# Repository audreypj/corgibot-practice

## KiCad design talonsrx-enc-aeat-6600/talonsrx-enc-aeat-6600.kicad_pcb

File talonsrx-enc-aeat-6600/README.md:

talonsrx-enc-aeat-6600
======================

A TalonSRX-compatible magnetic encoder with quadrature/incremental (A/B/I) and analog/absolute (PWM + cap) position output. This design implements the [AEAT-6600 sensor](https://github.com/ihartwig/frc-on-ftc-hw/blob/main/datasheets/AV02-2792EN-Data-Sheet-AEAT-6600-T16-2022-02-23.pdf) to use these outputs while also making the SSI/OTP pins available on a removable 6-pin programming header.

Accessing desired modes may (TBD?) [require OTP programming](https://github.com/ihartwig/frc-on-ftc-hw/blob/main/datasheets/av02-2791en_an_5501_aeat-6600_2014-04-21.pdf). It looks like the defaults are 8 CPR ABI incremental and no PWM absolute output.

The PCB is designed with 2 use cases in mind, though others may be possible
* (default) 3.3V operation from the [Data Port](https://store.ctr-electronics.com/content/user-manual/Talon%20SRX%20User's%20Guide.pdf) 0.05" pin header for incremental seeded by absolute position - HW default
    * Note that the Analog Input and Quadrature Index pins (3 & 9) differ between the TalonSRX and [Mag Encoder docs](https://store.ctr-electronics.com/content/user-manual/Magnetic%20Encoder%20User%27s%20Guide.pdf), so this design implements the pins described in the Mag Encoder docs to attempt compatibility.
* 5V operation from the 0.1" pin header for absolute position only - modify solder jumpers for 5V usage

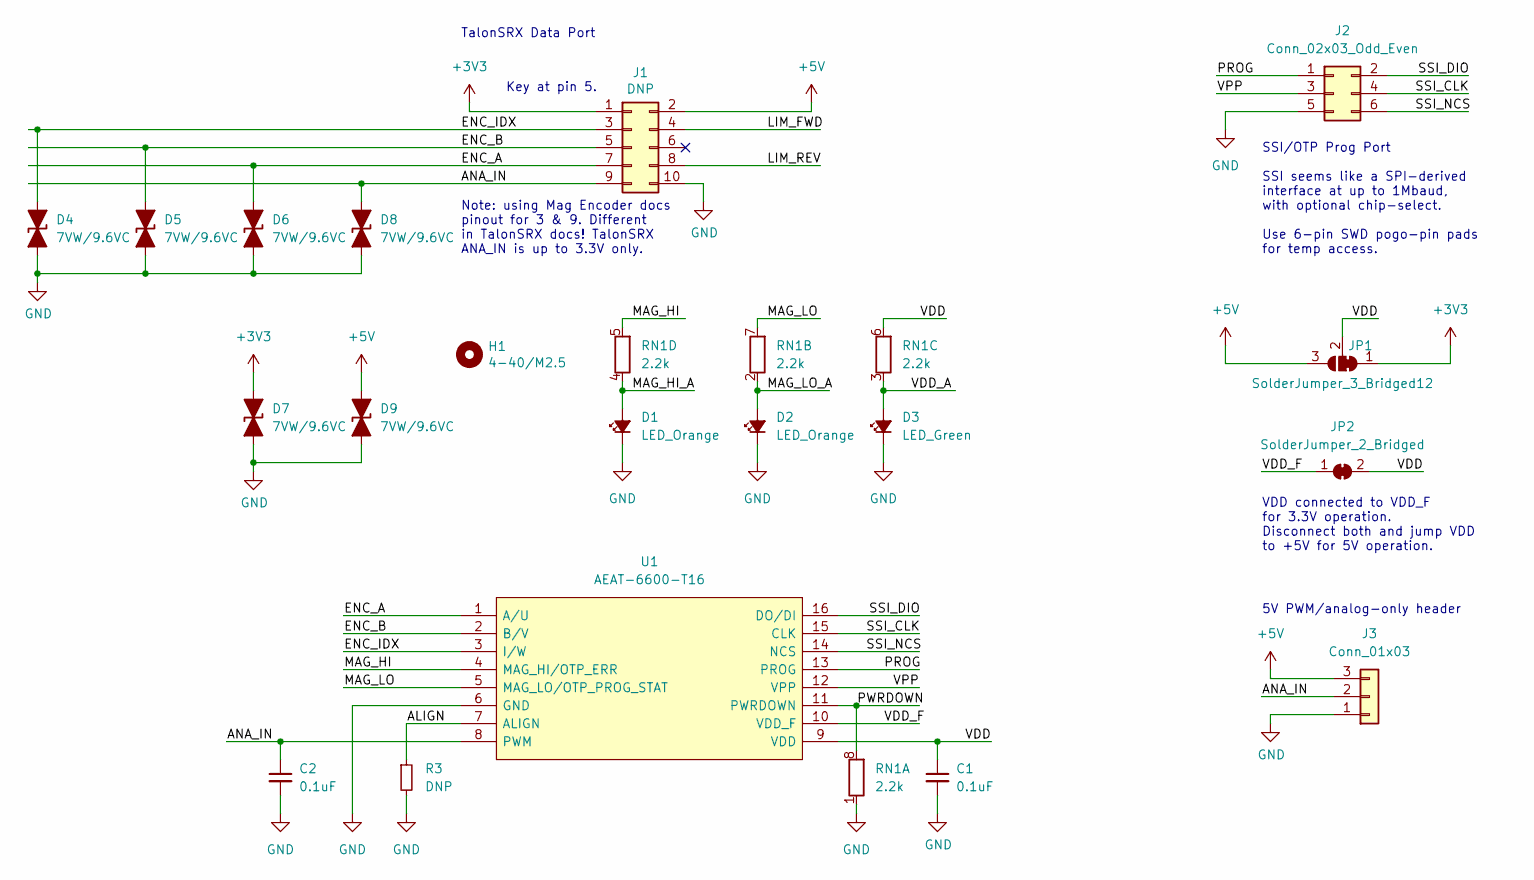
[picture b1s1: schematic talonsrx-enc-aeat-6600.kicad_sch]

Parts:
C1, C2: 0.1uF; C_0805_2012Metric
D1, D2: LED_Orange; LED_0603_1608Metric_FromBehind
D3: LED_Green; LED_0603_1608Metric_FromBehind
D4, D5, D6, D7, D8, D9: 7VW/9.6VC; D_0402_1005Metric_Pad0.77x0.64mm_HandSolder; Mfg PN PESD7V0L1BSLAZ
H1: 4-40/M2.5; MountingHole_2.7mm_M2.5
J1: DNP; PinHeader_2x05_P1.27mm_Vertical; Mfg PN 3221-10-0100-00
J2: Conn_02x03_Odd_Even; TC2030-NL_SMALL
J3: Conn_01x03; PinHeader_1x03_P2.54mm_Vertical
JP1: SolderJumper_3_Bridged12; SolderJumper-3_P1.3mm_Bridged12_RoundedPad1.0x1.5mm
JP2: SolderJumper_2_Bridged; SolderJumper-2_P1.3mm_Bridged_RoundedPad1.0x1.5mm
R3: DNP; R_0805_2012Metric
RN1: 2.2k; R_Array_Convex_4x0603; Mfg PN YC164-JR-072K2L
U1: AEAT-6600-T16; AEAT-6600-T16-SOP65P640X120-16N; Mfg PN AEAT-6600-T16; Mouser Part Number 630-AEAT-6600-T16

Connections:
+3V3: D7.1 (A1), J1.1, JP1.1 (A)
+5V: D9.1 (A1), J1.2, J3.3, JP1.3 (B)
/ALIGN: R3.1, U1.7 (ALIGN)
/ANA_IN: C2.1, D8.1 (A1), J1.9, J3.2, U1.8 (PWM)
/ENC_A: D6.1 (A1), J1.7, U1.1 (A/U)
/ENC_B: D5.1 (A1), J1.5, U1.2 (B/V)
/ENC_IDX: D4.1 (A1), J1.3, U1.3 (I/W)
/LIM_FWD: J1.4
/LIM_REV: J1.8
/MAG_HI: RN1.5 (R1.2), U1.4 (MAG_HI/OTP_ERR)
/MAG_HI_A: D1.2 (A), RN1.4 (R1.1)
/MAG_LO: RN1.7 (R1.2), U1.5 (MAG_LO/OTP_PROG_STAT)
/MAG_LO_A: D2.2 (A), RN1.2 (R1.1)
/PROG: J2.1, U1.13 (PROG)
/PWRDOWN: RN1.8 (R1.2), U1.11 (PWRDOWN)
/SSI_CLK: J2.4, U1.15 (CLK)
/SSI_DIO: J2.2, U1.16 (DO/DI)
/SSI_NCS: J2.6, U1.14 (NCS)
/VDD: C1.1, JP1.2 (C), JP2.2 (B), RN1.6 (R1.2), U1.9 (VDD)
/VDD_A: D3.2 (A), RN1.3 (R1.1)
/VDD_F: JP2.1 (A), U1.10 (VDD_F)
/VPP: J2.3, U1.12 (VPP)
GND: C1.2, C2.2, D1.1 (K), D2.1 (K), D3.1 (K), D4.2 (A2), D5.2 (A2), D6.2 (A2), D7.2 (A2), D8.2 (A2), D9.2 (A2), J1.10, J2.5, J3.1, R3.2, RN1.1 (R1.1), U1.6 (GND)

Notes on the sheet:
5V PWM/analog-only header
SSI/OTP Prog Port SSI seems like a SPI-derived interface at up to 1Mbaud, with optional chip-select. Use 6-pin SWD pogo-pin pads for temp access.
Key at pin 5.
TalonSRX Data Port
VDD connected to VDD_F for 3.3V operation. Disconnect both and jump VDD to +5V for 5V operation.
Note: using Mag Encoder docs pinout for 3 & 9. Different in TalonSRX docs! TalonSRX ANA_IN is up to 3.3V only.

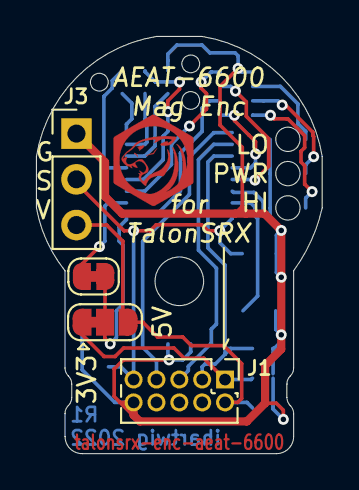
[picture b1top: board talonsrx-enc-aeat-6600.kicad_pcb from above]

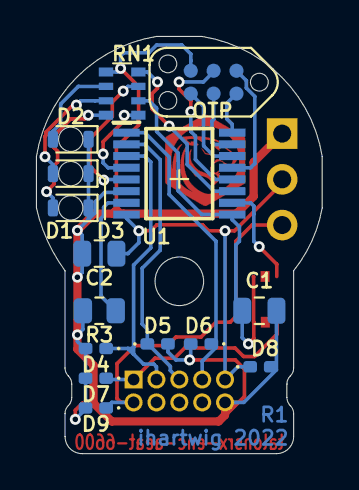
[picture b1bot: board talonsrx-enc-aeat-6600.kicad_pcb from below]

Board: 2 copper layers, 15.9 x 23.2 mm, 20 parts (15 on the bottom side), 21 nets.

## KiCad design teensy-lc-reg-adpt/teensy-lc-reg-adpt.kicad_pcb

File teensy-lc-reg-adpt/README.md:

teensy-lc-reg-adpt
==================

A backpack pcb for the [TeensyLC board](https://www.pjrc.com/teensy/teensyLC.html) to more easily add a [Pololu D24V5F5](https://www.pololu.com/product/2843) or similar voltage regulator to reach input voltages of up to 36V. This pairs well with the TeensyLC's 5V buffered output pin that can be used for PWM or small relay control. There is also a simple (R/R/C) input voltage monitoring circuit allowing the controller to take action on input voltage change.

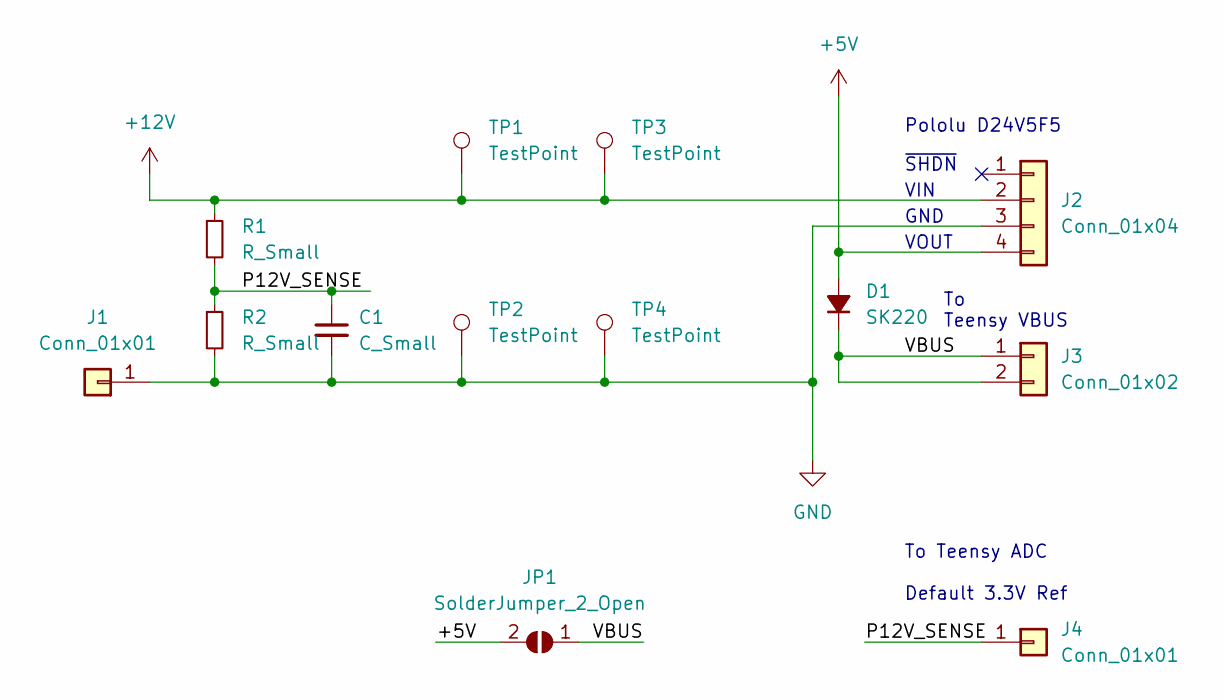
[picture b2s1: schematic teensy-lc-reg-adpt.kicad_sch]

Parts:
C1: C_Small; C_0805_2012Metric
D1: SK220; D_SMA
J1, J4: Conn_01x01; PinHeader_1x01_P2.54mm_Vertical
J2: Conn_01x04; PinHeader_1x04_P2.54mm_Vertical
J3: Conn_01x02; PinHeader_1x02_P2.54mm_Vertical
JP1: SolderJumper_2_Open; SolderJumper-2_P1.3mm_Open_TrianglePad1.0x1.5mm
R1, R2: R_Small; R_0805_2012Metric
TP1, TP2, TP3, TP4: TestPoint; TestPoint_Keystone_5019_Minature

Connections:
+5V: D1.2 (A), J2.4, JP1.2 (B)
+12V: J2.2, R1.1, TP1.1, TP3.1
/P12V_SENSE: C1.1, J4.1, R1.2, R2.1
/VBUS: D1.1 (K), J3.1, J3.2, JP1.1 (A)
GND: C1.2, J1.1, J2.3, R2.2, TP2.1, TP4.1

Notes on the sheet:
Pololu D24V5F5
~{SHDN}
To Teensy VBUS
To Teensy ADC Default 3.3V Ref
VIN
GND
VOUT

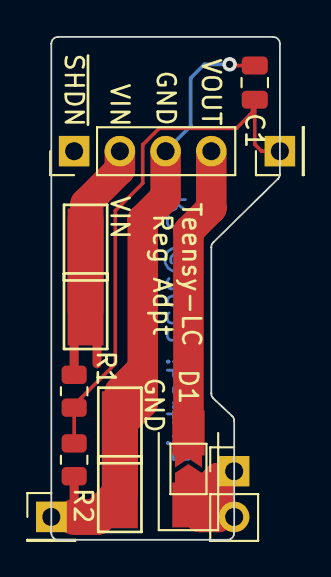
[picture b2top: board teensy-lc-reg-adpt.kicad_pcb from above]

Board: 2 copper layers, 12.7 x 27.9 mm, 13 parts (0 on the bottom side), 5 nets.

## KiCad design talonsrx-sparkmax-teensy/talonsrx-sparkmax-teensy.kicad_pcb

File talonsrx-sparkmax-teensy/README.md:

talonsrx-enc-limit-ftc
======================

TalonSRX breakout board for FTC-style Rev encoders and limit switches. Also has an extra Falcon-style limit switch connector.

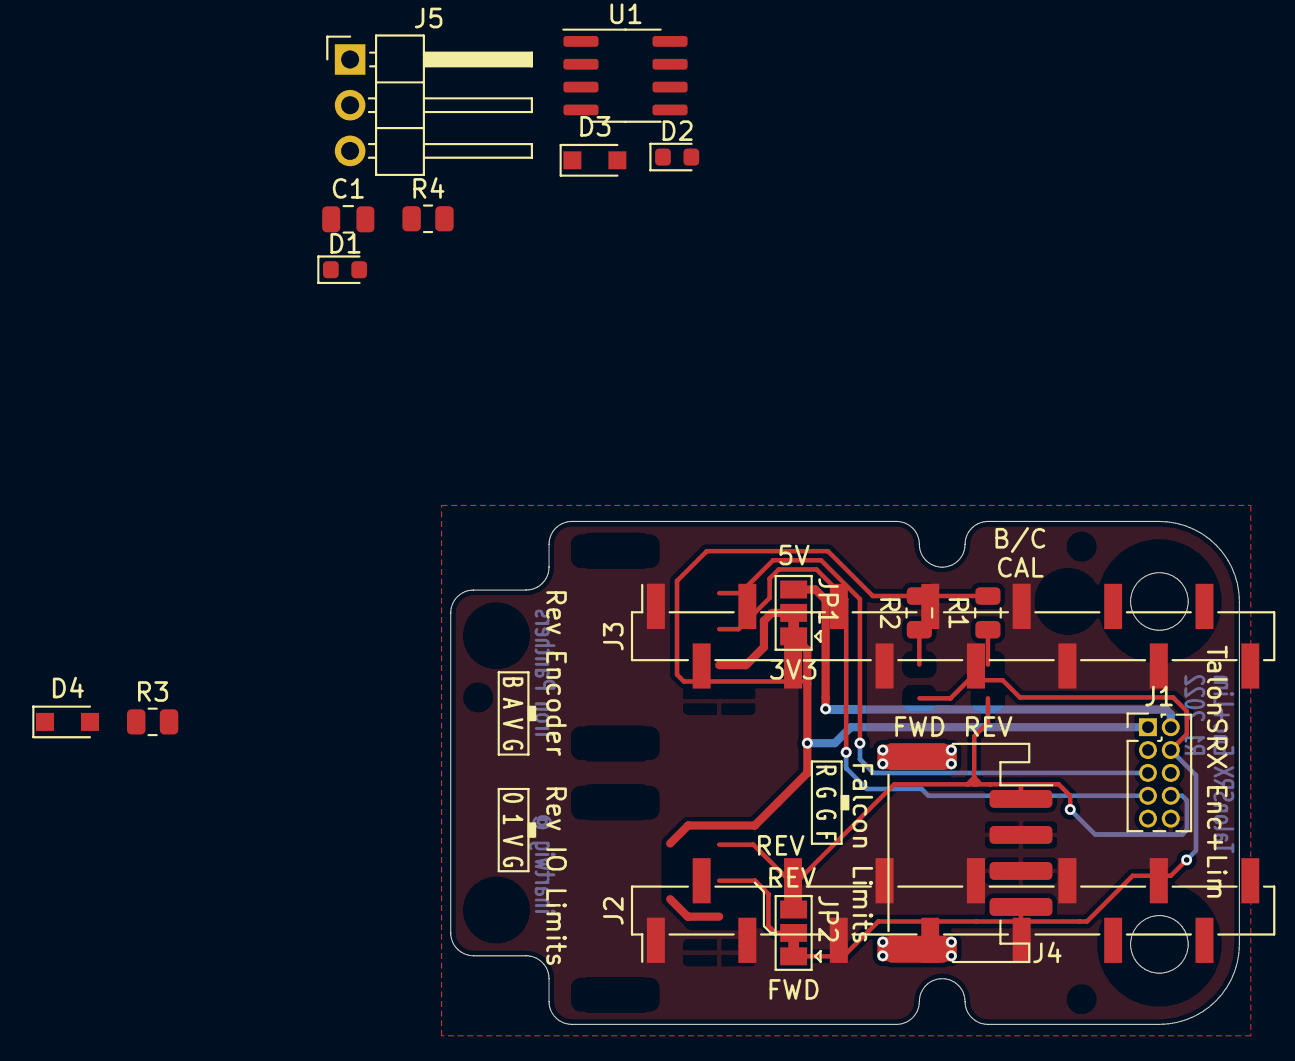
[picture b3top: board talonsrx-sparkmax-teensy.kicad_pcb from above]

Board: 2 copper layers, 43.8 x 27.9 mm, 19 parts (0 on the bottom side), 18 nets.

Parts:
C1: 0.1uF; C_0805_2012Metric
D1, D2: Green; LED_0603_1608Metric
D3: D_Small_Filled; D_SOD-323_HandSoldering
D4: DNP; D_SOD-323_HandSoldering
H1, H2: 4-40/M3; MountingHole_3.2mm_M3_Clearance
J1: DNP; PinHeader_2x05_P1.27mm_Vertical
J2: Conn_01x14; PinHeader_1x14_P2.54mm_Vertical_SMD_Pin1Left
J3: Conn_01x14; PinHeader_1x14_P2.54mm_Vertical_SMD_Pin1Right
J4: Conn_01x04; JST_PH_S4B-PH-SM4-TB_1x04-1MP_P2.00mm_Horizontal
J5: Conn_01x03; PinHeader_1x03_P2.54mm_Horizontal
JP1, JP2: SolderJumper_3_Bridged12; SolderJumper-3_P1.3mm_Bridged12_Pad1.0x1.5mm
R1, R2: 2.2k; R_0805_2012Metric
R3, R4: DNP; R_0805_2012Metric
U1: SN65HVD230; SOIC-8_3.9x4.9mm_P1.27mm

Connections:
+3V3: C1.1, D4.2 (A), J1.1, R3.1, U1.3 (VCC)
+5V: D3.2 (A), J1.2
/CAN_H: J5.3, U1.7 (CANH)
/CAN_L: J5.1, U1.6 (CANL)
/CAN_RS: R3.2, R4.1, U1.8 (Rs)
/CAN_RXD: JP2.2 (C), U1.4 (R)
/CAN_TXD: JP1.2 (C), U1.1 (D)
/D3_CANTX: J2.5, JP1.1 (A)
/D4_CANRX: J2.6, JP2.1 (A)
/D22_A8: J3.5, JP1.3 (B)
/D23_A9: J3.4, JP2.3 (B)
/LIM_FWD: J1.4, J4.4
/LIM_REV: J1.8, J4.1
/TSY_3V3: D4.1 (K), J3.3, R2.1
/TSY_3V3_A: D2.2 (A), R2.2
/TSY_VIN: D3.1 (K), J3.1, R1.1
/TSY_VIN_A: D1.2 (A), R1.2
GND: C1.2, D1.1 (K), D2.1 (K), J1.10, J2.1, J4.2, J4.3, R4.2, U1.2 (GND)

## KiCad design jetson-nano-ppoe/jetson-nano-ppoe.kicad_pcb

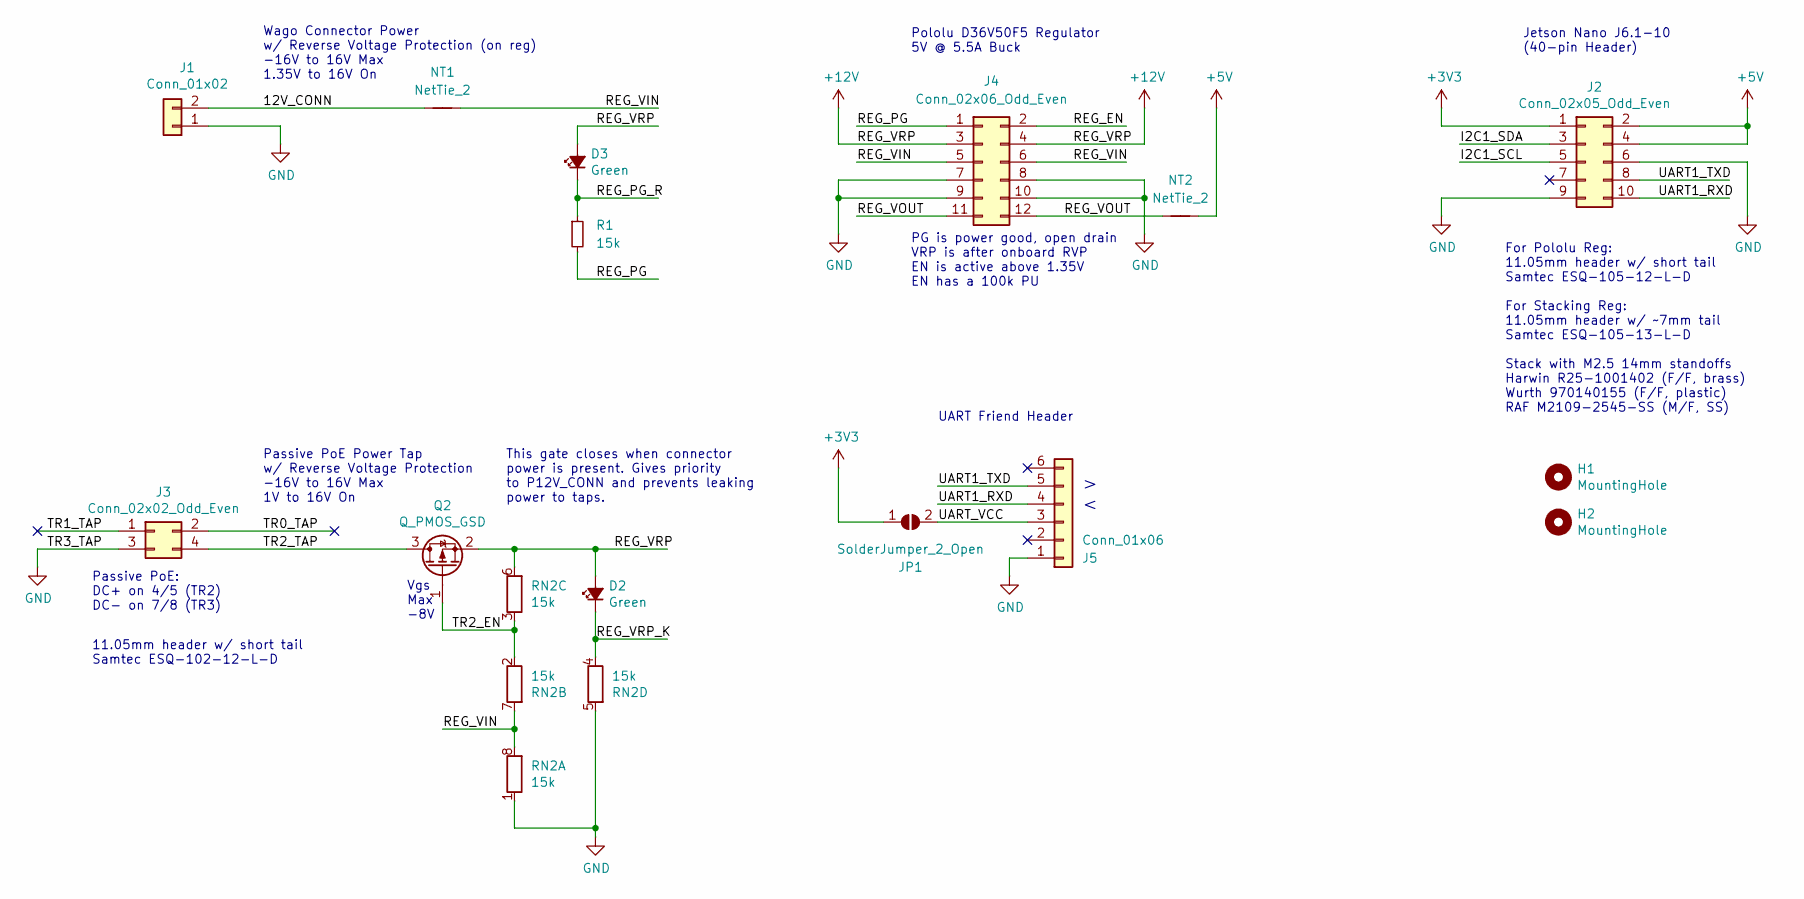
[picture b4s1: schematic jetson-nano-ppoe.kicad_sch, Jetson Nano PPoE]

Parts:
D2, D3: Green; LED_0603_1608Metric
H1, H2: MountingHole; MountingHole_3.2mm_M3_Pad_Via
J1: Conn_01x02; WAGO_250-202
J2: Conn_02x05_Odd_Even; Pin_Header_Straight_2x05_Pitch2.54mm
J3: Conn_02x02_Odd_Even; PinHeader_2x02_P2.54mm_Vertical
J4: Conn_02x06_Odd_Even; PinHeader_2x06_P2.54mm_Vertical
J5: Conn_01x06; PinHeader_1x06_P2.54mm_Vertical
JP1: SolderJumper_2_Open; SolderJumper-2_P1.3mm_Open_TrianglePad1.0x1.5mm
NT1, NT2: NetTie_2; NetTie-2_SMD_Pad2.0mm
Q2: Q_PMOS_GSD; SOT-23; Mfg PN SI2305B
R1: 15k; R_0805_2012Metric
RN2: 15k; R_Array_Convex_4x1206; Mfg PN YC164-JR-0715KL

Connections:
+3V3: J2.1, JP1.1 (A)
+5V: J2.2, J2.4, NT2.1
+12V: D2.2 (A), D3.2 (A), J4.3, J4.4, Q2.2 (S), RN2.6 (R1.2)
/12V_CONN: J1.2, NT1.1
/I2C1_SCL: J2.5
/I2C1_SDA: J2.3
/REG_EN: J4.2
/REG_PG: J4.1, R1.2
/REG_PG_R: D3.1 (K), R1.1
/REG_VIN: J4.5, J4.6, NT1.2, RN2.7 (R1.2), RN2.8 (R1.2)
/REG_VOUT: J4.11, J4.12, NT2.2
/REG_VRP_K: D2.1 (K), RN2.4 (R1.1)
/TR0_TAP: J3.2
/TR1_TAP: J3.1
/TR2_EN: Q2.1 (G), RN2.2 (R1.1), RN2.3 (R1.1)
/TR2_TAP: J3.4, Q2.3 (D)
/UART1_RXD: J2.10, J5.4
/UART1_TXD: J2.8, J5.5
/UART_VCC: J5.3, JP1.2 (B)
GND: J1.1, J2.6, J2.9, J3.3, J4.7, J4.8, J4.9, J4.10, J5.1, RN2.1 (R1.1), RN2.5 (R1.2)

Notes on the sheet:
UART Friend Header
Passive PoE: DC+ on 4/5 (TR2) DC- on 7/8 (TR3)
Jetson Nano J6.1-10 (40-pin Header)
Passive PoE Power Tap w/ Reverse Voltage Protection -16V to 16V Max 1V to 16V On
> <
Pololu D36V50F5 Regulator 5V @ 5.5A Buck
Vgs Max -8V
This gate closes when connector power is present. Gives priority to P12V_CONN and prevents leaking power to taps.
Wago Connector Power w/ Reverse Voltage Protection (on reg) -16V to 16V Max 1.35V to 16V On
11.05mm header w/ short tail Samtec ESQ-102-12-L-D
For Pololu Reg: 11.05mm header w/ short tail Samtec ESQ-105-12-L-D For Stacking Reg: 11.05mm header w/ ~7mm tail Samtec ESQ-105-13-L-D Stack with M2.5 14mm standoffs Harwin R25-1001402 (F/F, brass) Wurth 970140155 (F/F, plastic) RAF M2109-2545-SS (M/F, SS)
PG is power good, open drain VRP is after onboard RVP EN is active above 1.35V EN has a 100k PU

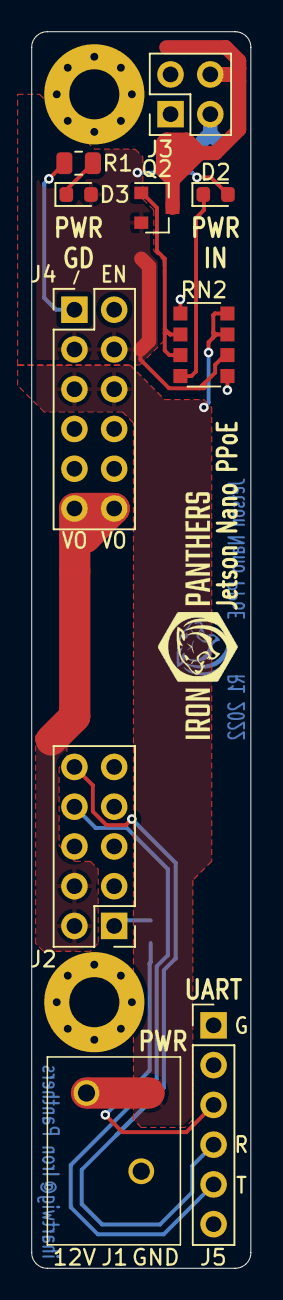
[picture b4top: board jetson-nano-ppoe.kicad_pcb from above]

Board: 2 copper layers, 14.0 x 79.0 mm, 15 parts (1 on the bottom side), 15 nets.

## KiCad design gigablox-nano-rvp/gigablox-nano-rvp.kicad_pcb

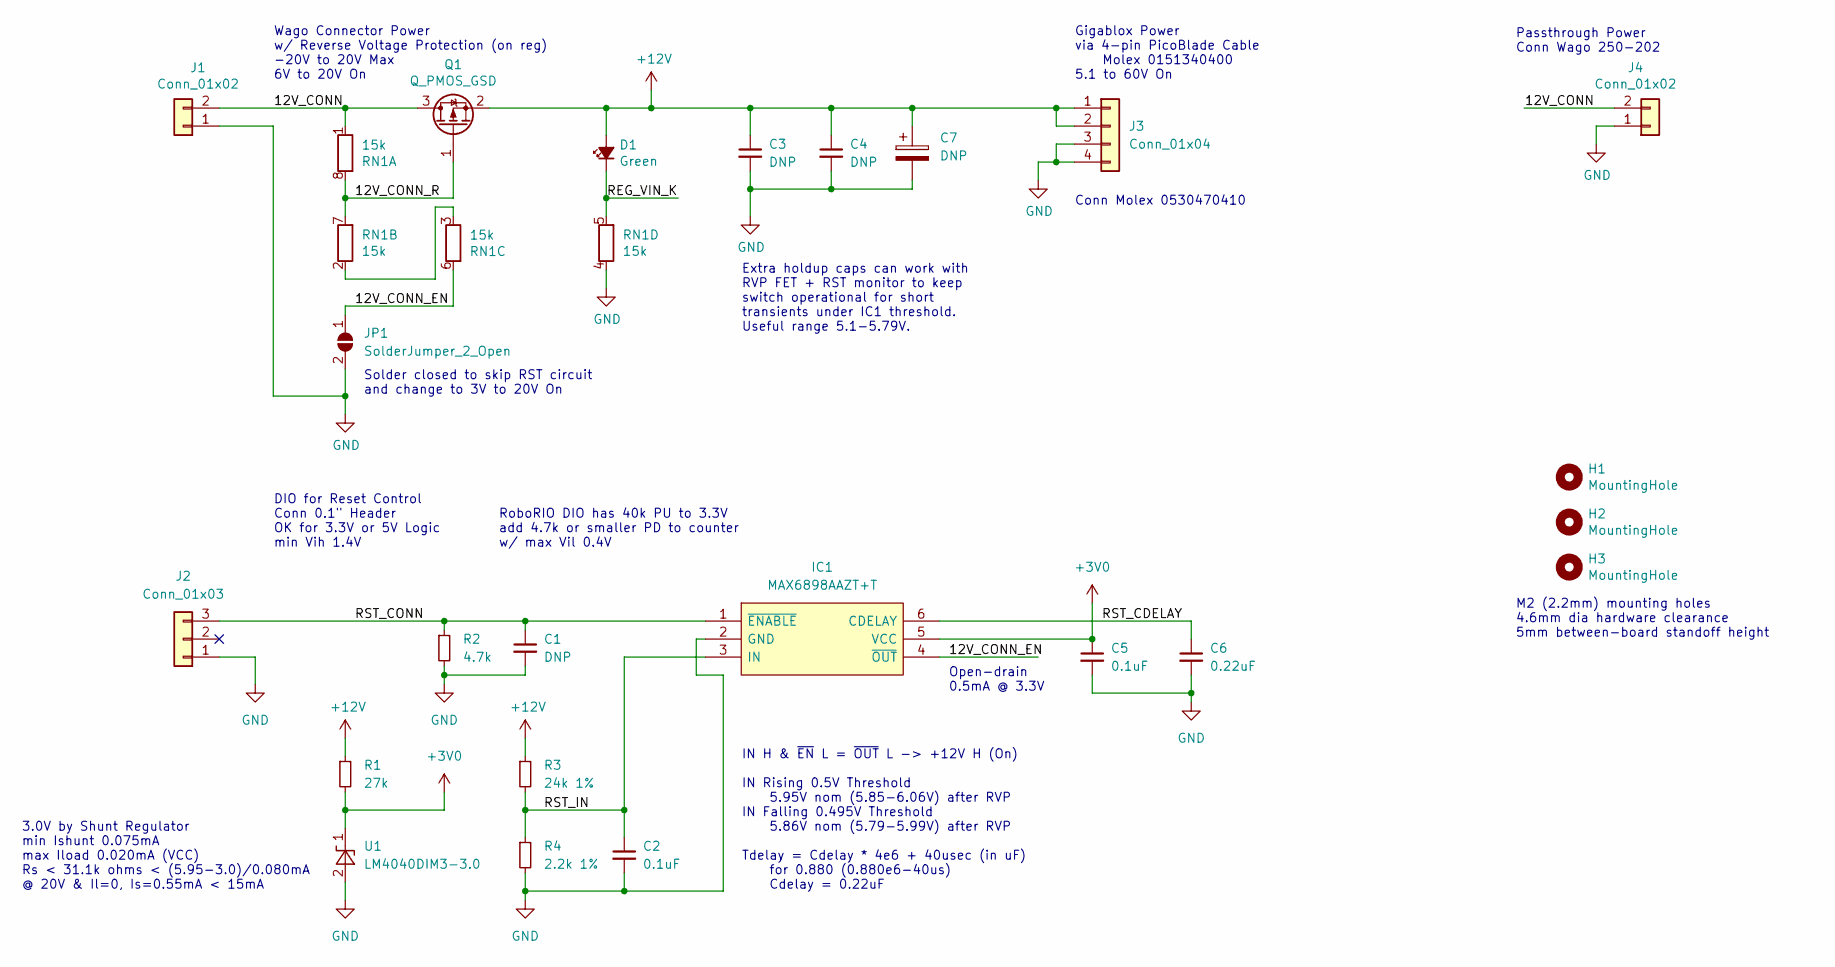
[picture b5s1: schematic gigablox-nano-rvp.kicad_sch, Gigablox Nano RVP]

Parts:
C1, C3, C4: DNP; C_0805_2012Metric
C2, C5: 0.1uF; C_0805_2012Metric
C6: 0.22uF; C_0805_2012Metric
C7: DNP; CP_Radial_D6.3mm_P2.50mm
D1: Green; LED_0603_1608Metric
H1, H2, H3: MountingHole; MountingHole_2.2mm_M2
IC1: MAX6898AAZT+T; SOT-23-6; Mfg PN MAX6898AAZT+T; Mouser Part Number 700-MAX6898AAZTT
J1, J4: Conn_01x02; WAGO_250-202; Mfg PN 250-202
J2: Conn_01x03; PinHeader_1x03_P2.54mm_Vertical
J3: Conn_01x04; 0530470410; Mfg PN 0530470410
JP1: SolderJumper_2_Open; SolderJumper-2_P1.3mm_Open_TrianglePad1.0x1.5mm
Q1: Q_PMOS_GSD; SOT-23; Mfg PN SI2305B
R1: 27k; R_0805_2012Metric
R2: 4.7k; R_0805_2012Metric
R3: 24k 1%; R_0805_2012Metric
R4: 2.2k 1%; R_0805_2012Metric
RN1: 15k; R_Array_Convex_4x1206; Mfg PN YC164-JR-0715KL
U1: LM4040DIM3-3.0; SOT-23; Mfg PN LM4040DEM3-3.0+T

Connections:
+3V0: C5.1, IC1.5 (VCC), R1.2, U1.1 (K)
+12V: C3.1, C4.1, C7.1, D1.2 (A), J3.1, J3.2, Q1.2 (S), R1.1, R3.1
/12V_CONN: J1.2, J4.2, Q1.3 (D), RN1.1 (R1.1)
/12V_CONN_EN: IC1.4 (~OUT), JP1.1 (A), RN1.6 (R1.2)
/12V_CONN_R: Q1.1 (G), RN1.7 (R1.2), RN1.8 (R1.2)
/REG_VIN_K: D1.1 (K), RN1.5 (R1.2)
/RST_CDELAY: C6.1, IC1.6 (CDELAY)
/RST_CONN: C1.1, IC1.1 (~ENABLE), J2.3, R2.1
/RST_IN: C2.1, IC1.3 (IN), R3.2, R4.1
GND: C1.2, C2.2, C3.2, C4.2, C5.2, C6.2, C7.2, IC1.2 (GND), J1.1, J2.1, J3.3, J3.4, J4.1, JP1.2 (B), R2.2, R4.2, RN1.4 (R1.1), U1.2 (A)
unnamed: RN1.2 (R1.1), RN1.3 (R1.1)

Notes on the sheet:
Solder closed to skip RST circuit and change to 3V to 20V On
Extra holdup caps can work with RVP FET + RST monitor to keep switch operational for short transients under IC1 threshold. Useful range 5.1-5.79V.
IN H & ~{EN} L = ~{OUT} L -> +12V H (On) IN Rising 0.5V Threshold 5.95V nom (5.85-6.06V) after RVP IN Falling 0.495V Threshold 5.86V nom (5.79-5.99V) after RVP Tdelay = Cdelay * 4e6 + 40usec (in uF) for 0.880 (0.880e6-40us) Cdelay = 0.22uF
M2 (2.2mm) mounting holes 4.6mm dia hardware clearance 5mm between-board standoff height
Gigablox Power via 4-pin PicoBlade Cable Molex 0151340400 5.1 to 60V On
Wago Connector Power w/ Reverse Voltage Protection (on reg) -20V to 20V Max 6V to 20V On
DIO for Reset Control Conn 0.1" Header OK for 3.3V or 5V Logic min Vih 1.4V
Conn Molex 0530470410
3.0V by Shunt Regulator min Ishunt 0.075mA max Iload 0.020mA (VCC) Rs < 31.1k ohms < (5.95-3.0)/0.080mA @ 20V & Il=0, Is=0.55mA < 15mA
RoboRIO DIO has 40k PU to 3.3V add 4.7k or smaller PD to counter w/ max Vil 0.4V
Passthrough Power Conn Wago 250-202
Open-drain 0.5mA @ 3.3V

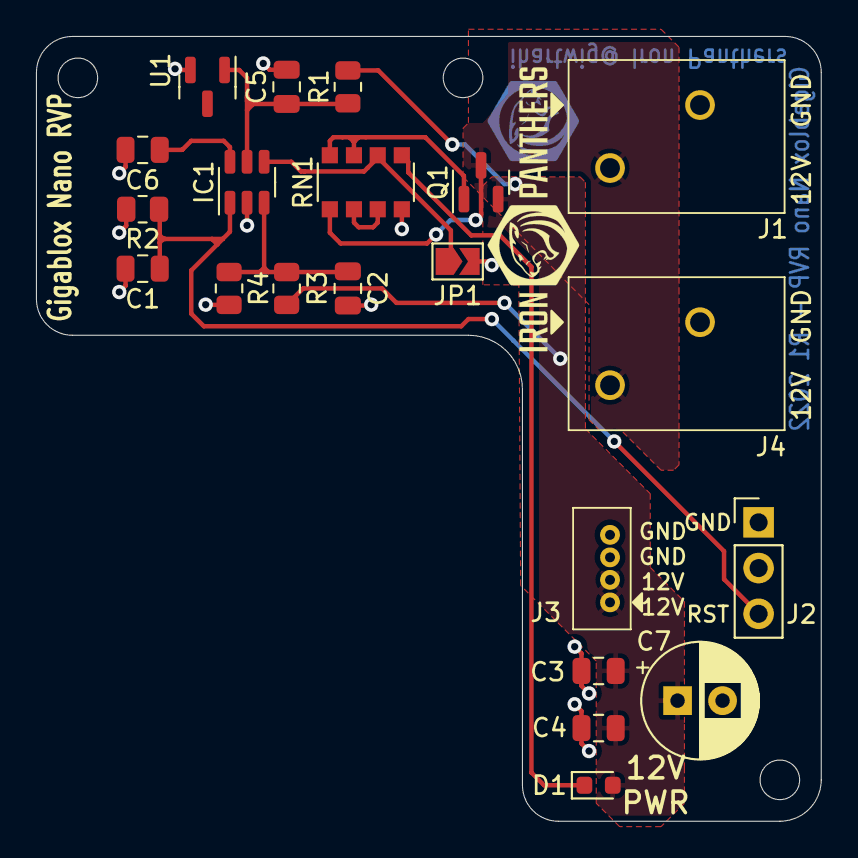
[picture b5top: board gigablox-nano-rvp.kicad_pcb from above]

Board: 2 copper layers, 43.6 x 43.6 mm, 24 parts (0 on the bottom side), 11 nets.

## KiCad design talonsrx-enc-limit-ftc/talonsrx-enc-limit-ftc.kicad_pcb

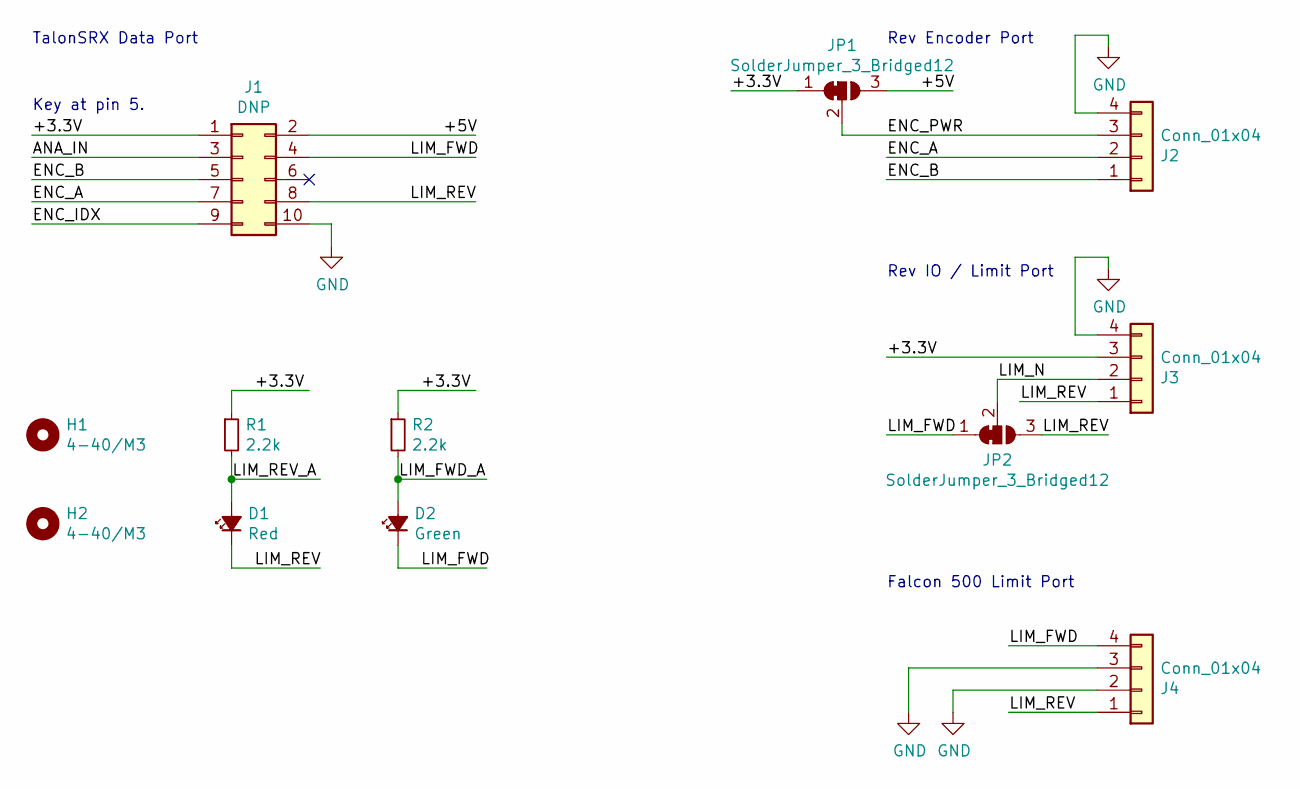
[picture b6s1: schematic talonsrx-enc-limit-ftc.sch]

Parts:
D1: Red; LED_0805_2012Metric; Mfg PN C2293; JLCPCB PN C2293
D2: Green; LED_0805_2012Metric; Mfg PN C2292; JLCPCB PN C2292
H1, H2: 4-40/M3; MountingHole_3.2mm_M3_Clearance
J1: DNP; PinHeader_2x05_P1.27mm_Vertical; Mfg PN 20021311-00010T4LF
J2, J3, J4: Conn_01x04; JST_PH_S4B-PH-SM4-TB_1x04-1MP_P2.00mm_Horizontal; Mfg PN S4B-PH-SM4-K-TB(LF)(SN); JLCPCB PN C265332
JP1, JP2: SolderJumper_3_Bridged12; SolderJumper-3_P1.3mm_Bridged12_Pad1.0x1.5mm
R1, R2: 2.2k; R_0805_2012Metric; Mfg PN 0805W8F2201T5E; JLCPCB PN C17520

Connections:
/+3.3V: J1.1, J3.3, JP1.1 (A), R1.1, R2.1
/+5V: J1.2, JP1.3 (B)
/ANA_IN: J1.3
/ENC_A: J1.7, J2.2
/ENC_B: J1.5, J2.1
/ENC_IDX: J1.9
/ENC_PWR: J2.3, JP1.2 (C)
/LIM_FWD: D2.1 (K), J1.4, J4.4, JP2.1 (A)
/LIM_FWD_A: D2.2 (A), R2.2
/LIM_N: J3.2, JP2.2 (C)
/LIM_REV: D1.1 (K), J1.8, J3.1, J4.1, JP2.3 (B)
/LIM_REV_A: D1.2 (A), R1.2
GND: J1.10, J2.4, J3.4, J4.2, J4.3

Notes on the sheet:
Key at pin 5.
TalonSRX Data Port
Rev Encoder Port
Rev IO / Limit Port
Falcon 500 Limit Port

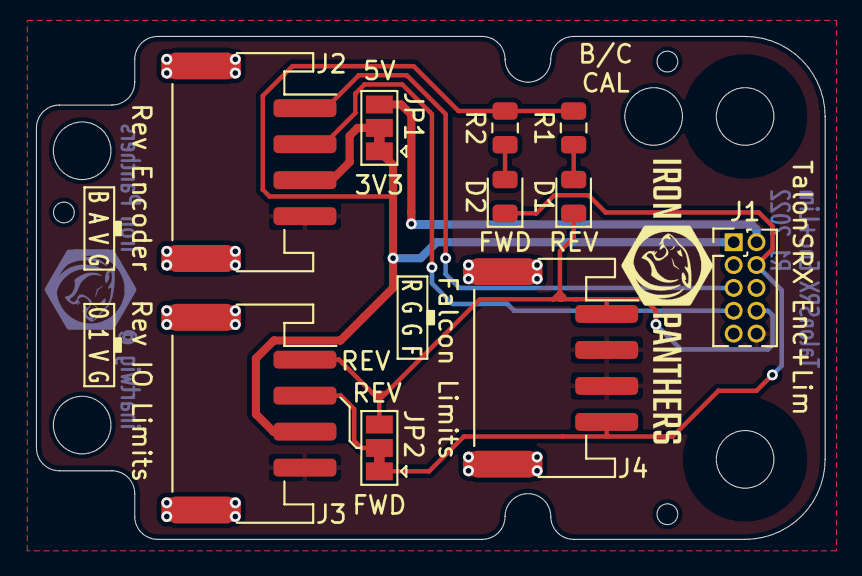
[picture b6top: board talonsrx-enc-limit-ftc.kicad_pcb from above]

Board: 2 copper layers, 43.8 x 27.9 mm, 12 parts (0 on the bottom side), 11 nets.

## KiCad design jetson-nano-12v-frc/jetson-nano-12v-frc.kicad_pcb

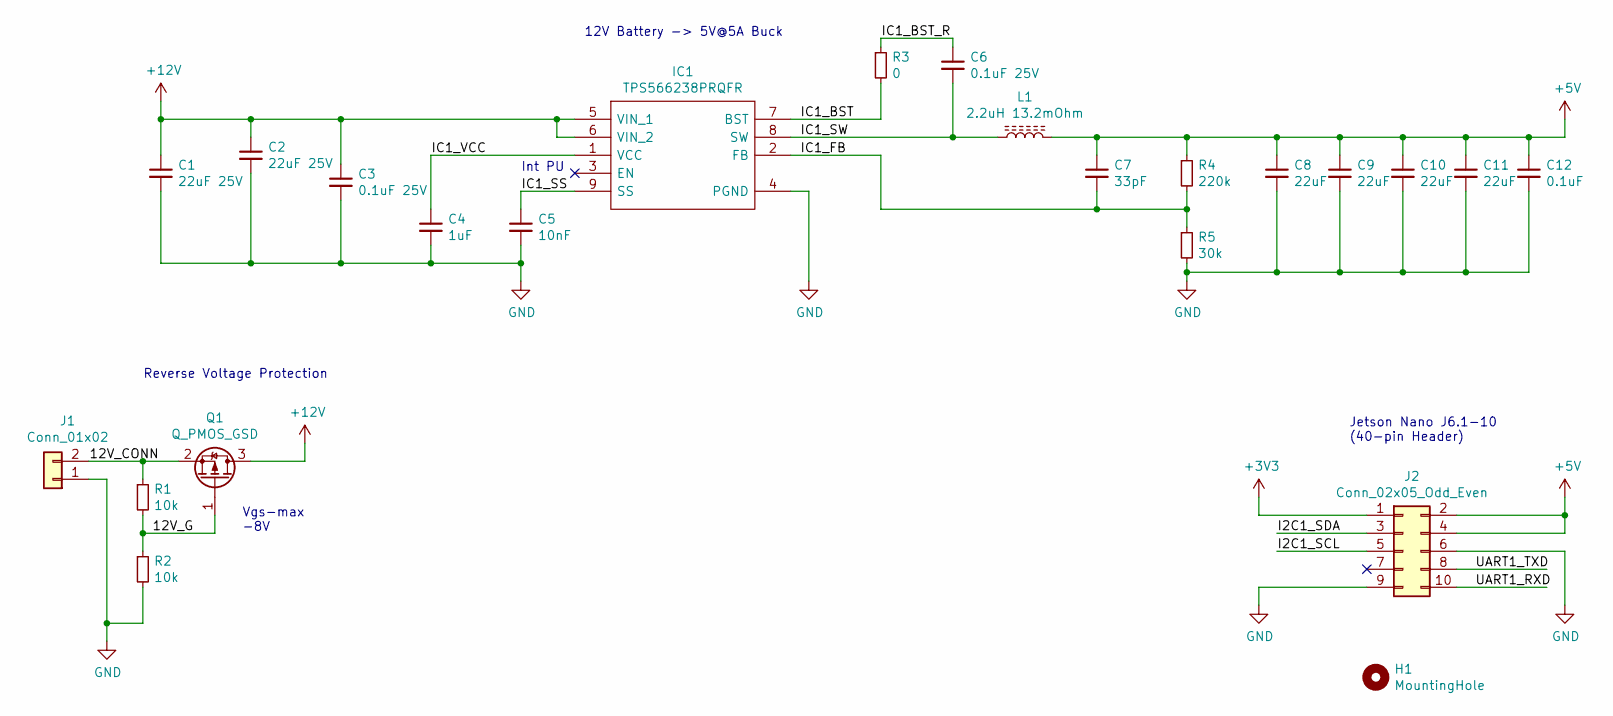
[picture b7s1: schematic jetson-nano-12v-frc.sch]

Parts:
C1, C2: 22uF 25V; C_0805
C3, C6: 0.1uF 25V; C_0603
C4: 1uF; C_0603
C5: 10nF; C_0603
C7: 33pF; C_0603
C8, C9, C10, C11: 22uF; C_0805
C12: 0.1uF; C_0603
H1: MountingHole; MountingHole_3.2mm_M3_Pad_Via
IC1: TPS566238PRQFR; Manufacturer_Part_Number TPS566238PRQFR
J1: Conn_01x02; WAGO_250-202
J2: Conn_02x05_Odd_Even; Pin_Header_Straight_2x05_Pitch2.54mm
L1: 2.2uH 13.2mOhm; L_Coilcraft_XAL5030; Mfg PN XAL5030-222MEB
Q1: Q_PMOS_GSD; SOT-23; Mfg PN SI2305B
R1, R2: 10k; R_0603
R3: 0; R_0603
R4: 220k; R_0603
R5: 30k; R_0603

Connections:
+3V3: J2.1
+5V: C7.1, C8.1, C9.1, C10.1, C11.1, C12.1, J2.2, J2.4, L1.2, R4.1
+12V: C1.1, C2.1, C3.1, IC1.5 (VIN_1), IC1.6 (VIN_2), Q1.3 (D)
/12V_CONN: J1.2, Q1.2 (S), R1.1
/12V_G: Q1.1 (G), R1.2, R2.1
/I2C1_SCL: J2.5
/I2C1_SDA: J2.3
/IC1_BST: IC1.7 (BST), R3.2
/IC1_BST_R: C6.1, R3.1
/IC1_FB: C7.2, IC1.2 (FB), R4.2, R5.1
/IC1_SS: C5.1, IC1.9 (SS)
/IC1_SW: C6.2, IC1.8 (SW), L1.1
/IC1_VCC: C4.1, IC1.1 (VCC)
/UART1_RXD: J2.10
/UART1_TXD: J2.8
GND: C1.2, C2.2, C3.2, C4.2, C5.2, C8.2, C9.2, C10.2, C11.2, C12.2, IC1.4 (PGND), J1.1, J2.6, J2.9, R2.2, R5.2

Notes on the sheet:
Jetson Nano J6.1-10 (40-pin Header)
Vgs-max -8V
Reverse Voltage Protection
12V Battery -> 5V@5A Buck
Int PU

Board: 2 copper layers, 23 parts (0 on the bottom side), 11 nets, no tracks yet.

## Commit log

2022-04-21 init repo and add talonsrx-enc-limit-ftc
2022-04-21 talonsrx-enc-limit-ftc R1 gerbers
2022-04-21 license and readme
2022-04-21 talonsrx-enc-limit-ftc R1 gerbers again
2022-04-23 sch for jetson-nano-12v-frc
2022-04-29 change jetson-nano-12v-frc to jetson-nano-ppoe and floorplan
2022-04-30 jetson-nano-ppoe more floorplan and spice model attempt
2022-04-30 jetson-nano-ppoe layout r1
2022-04-30 more R1 gerbers
2022-05-03 add roborio proto r1
2022-05-03 roborio-proto and talonsrx-enc-limit-ftc gerbers again
2022-05-04 talonsrx-enc-limit-ftc for jlcpcb asm and fix pinouts
2022-06-29 update jetson-nano-ppoe for pololu reg
2022-06-29 new jetson-nano-ppoe gerbers
2022-07-03 add gigablox-nano-rvp and simplify jetson-nano-ppoe
2022-07-03 gigablox-nano-rvp floorplan
2022-07-06 new jetson-nano-ppoe and gigablox-nano-rvp gerbers
2022-07-11 gigablox-nano-rvp and jetson-nano-ppoe gerbers
2022-07-11 gigablox-nano-rvp and jetson-nano-ppoe boms
2022-07-23 add frc2022-mecanum-drive-ex base code
2022-07-23 add frc2022-mecanum-drive-ex auto selections
2022-07-23 fix frc2022-mecanum-drive-ex default configs
2022-07-24 add frc2022-mecanum-drive-ex velocity control
2022-10-31 add interim updates and talonsrx-sparkmax-teensy in progress
2022-10-31 add teensy-lc-reg-adpt
2022-10-31 fix teensy-lc-reg-adpt gerbers
2022-11-07 add teensy-4-can1
2022-11-24 update teensy-lc-reg-adpt R2 with Vin monitor
2022-12-28 add talonsrx-enc-aeat-6600 r1
2022-12-28 update readme and docs

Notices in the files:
teensy-lc-reg-adpt/teensy-lc-reg-adpt.kicad_pcb:
R2 ©2022 ihartwig
